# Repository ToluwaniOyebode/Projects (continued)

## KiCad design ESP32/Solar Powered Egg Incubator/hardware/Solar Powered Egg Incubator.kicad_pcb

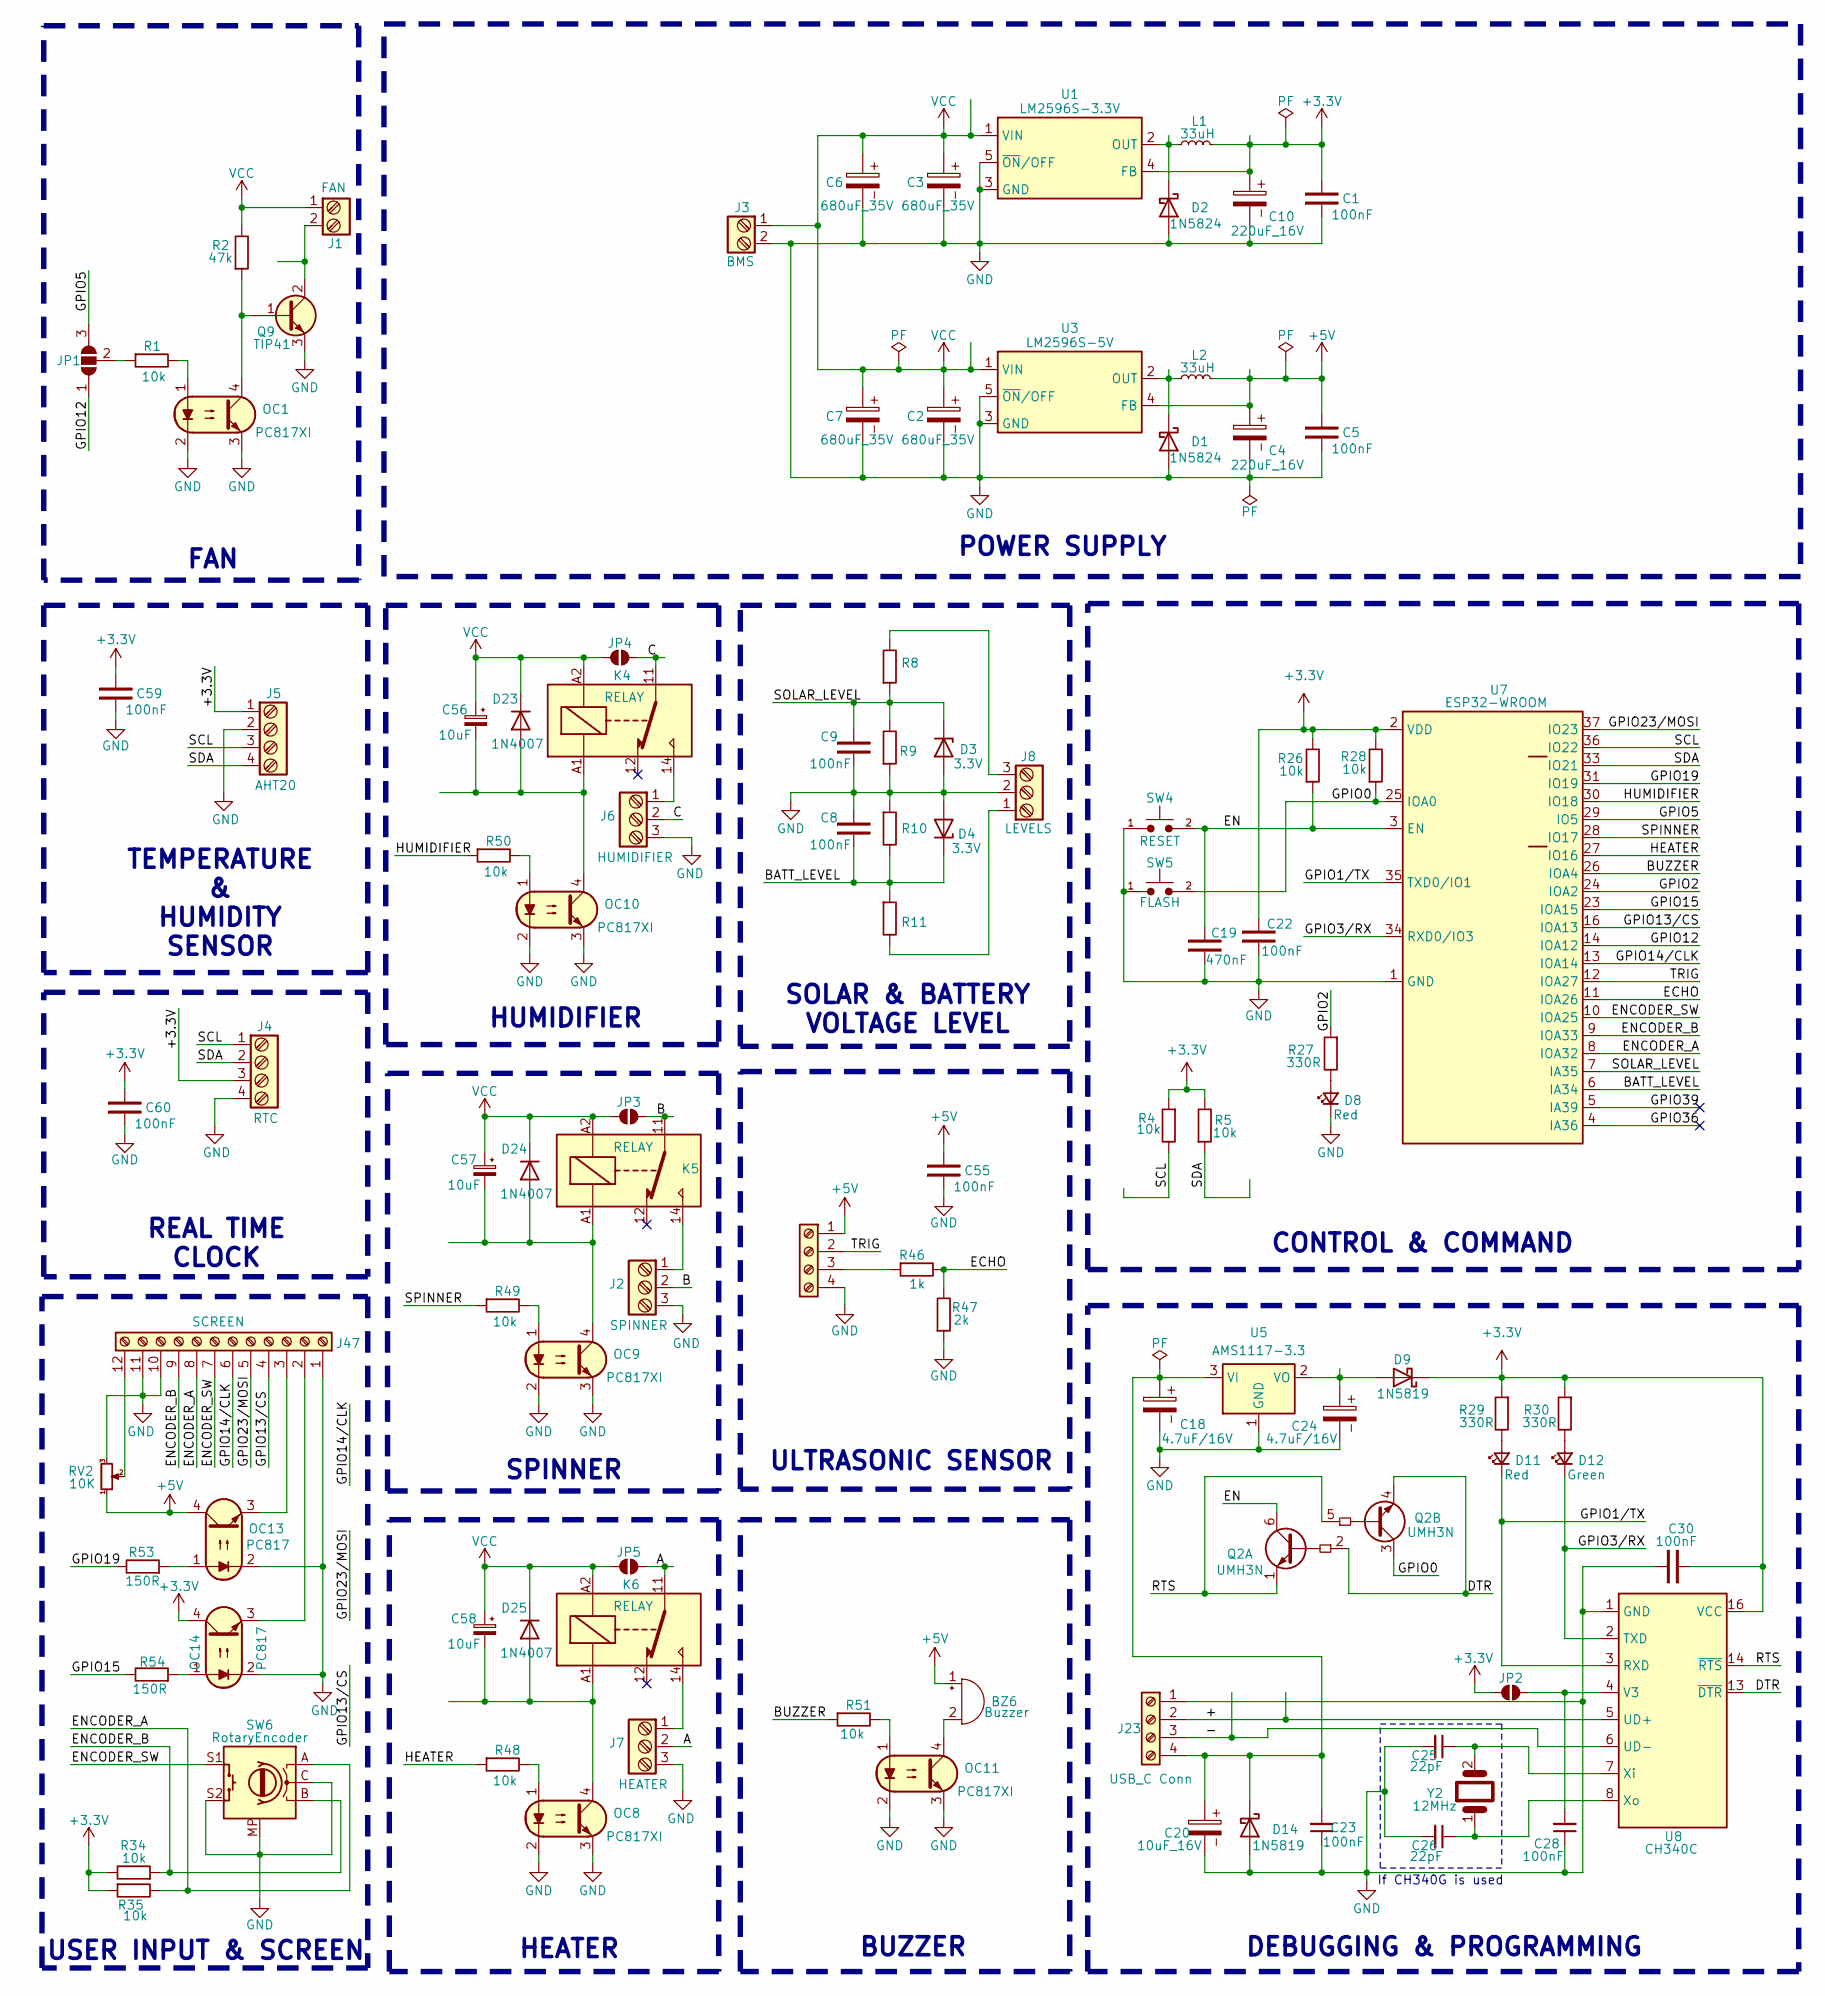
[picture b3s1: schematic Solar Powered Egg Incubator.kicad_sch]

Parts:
BZ6: Buzzer; Buzzer_15x7.5RM7.6
C1, C5, C8, C9, C22, C23, C28, C30, C55, C59, C60: 100nF; C_0805_2012Metric_Pad1.18x1.45mm_HandSolder
C2, C3, C6, C7: 680uF_35V; CP_Elec_10x12.5
C4, C10: 220uF_16V; CP_Elec_6.3x7.7
C18, C24: 4.7uF/16V; CP_EIA-3528-21_Kemet-B_HandSolder
C19: 470nF; C_0805_2012Metric_Pad1.18x1.45mm_HandSolder
C20: 10uF_16V; CP_Radial_D5.0mm_P2.00mm
C25, C26: 22pF; C_0805_2012Metric_Pad1.18x1.45mm_HandSolder
C56, C57, C58: 10uF; CP_EIA-3528-21_Kemet-B_HandSolder
D1, D2: 1N5824; D_SMA
D3, D4: 3.3V; D_SOD-123
D8, D11: Red; LED_D3.0mm
D9, D14: 1N5819; D_SMA
D12: Green; LED_D3.0mm
D23, D24, D25: 1N4007; D_SMA
J1: FAN; TerminalBlock_Phoenix_PT-1,5-2-5.0-H_1x02_P5.00mm_Horizontal
J2: SPINNER; TerminalBlock_Phoenix_MKDS-1,5-3_1x03_P5.00mm_Horizontal
J3: BMS; TerminalBlock_Phoenix_PT-1,5-2-5.0-H_1x02_P5.00mm_Horizontal
J4: RTC; PinHeader_1x04_P2.54mm_Vertical
J5: AHT20; PinHeader_1x04_P2.54mm_Vertical
J6: HUMIDIFIER; TerminalBlock_Phoenix_MKDS-1,5-3_1x03_P5.00mm_Horizontal
J7: HEATER; TerminalBlock_Phoenix_MKDS-1,5-3_1x03_P5.00mm_Horizontal
J8: LEVELS; PinHeader_1x03_P2.54mm_Vertical
J23: USB_C Conn; PinHeader_1x04_P2.54mm_Vertical
J42: Ultra Sonic; PinSocket_1x04_P2.54mm_Vertical
J47: SCREEN; PinHeader_1x12_P2.54mm_Vertical
JP1: SolderJumper_3_Open; SolderJumper-3_P1.3mm_Open_Pad1.0x1.5mm
JP2, JP3, JP4, JP5: SolderJumper-2_P1.3mm_Open_Pad1.0x1.5mm
K4, K5, K6: RELAY; Relay_SPDT_Finder_36.11
L1, L2: 33uH; L_12x12mm_H6mm
OC1, OC8, OC9, OC10, OC11: PC817XI; SMDIP-4_W9.53mm
OC13, OC14: PC817; SMDIP-4_W9.53mm
Q2: UMH3N; SOT-363_SC-70-6
Q9: TIP41; TO-220-3_Vertical
R1, R4, R5, R26, R28, R34, R35, R48, R49, R50, R51: 10k; R_0805_2012Metric
R2: 47k; R_0805_2012Metric
R8, R9, R10, R11: NS; R_0805_2012Metric
R27, R29, R30: 330R; R_0805_2012Metric
R46: 1k; R_0805_2012Metric
R47: 2k; R_0805_2012Metric
R53, R54: 150R; R_0805_2012Metric
RV2: 10K; Potentiometer_Bourns_3296W_Vertical
SW4: RESET; SW_SPST_CK_KXT3
SW5: FLASH; SW_SPST_CK_KXT3
SW6: RotaryEncoder; PinHeader_1x06_P2.54mm_Vertical
U1: LM2596S-3.3V; TO-263-5_TabPin6
U3: LM2596S-5V; TO-263-5_TabPin6
U5: AMS1117-3.3; SOT-223-3_TabPin2
U7: ESP32-WROOM; ESP32-WROOM-32
U8: CH340C; SOIC-16_3.9x9.9mm_P1.27mm
Y2: 12MHz; Crystal_HC49-4H_Vertical

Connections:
+3.3V: C1.2, C10.1, C22.2, C30.1, C59.2, C60.2, D9.1 (K), J4.3, J5.1, JP2.2 (B), L1.2, OC14.4, R4.1, R5.2, R26.2, R28.2, R29.1, R30.1, R34.2, R35.1, U1.4 (FB), U7.2 (VDD), U8.16 (VCC)
+5V: BZ6.1 (+), C4.1, C5.2, C55.2, J42.1, L2.2, OC13.4, RV2.1, U3.4 (FB)
/+: J23.2, U8.5 (UD+)
/-: J23.3, U8.6 (UD-)
/A: J7.2, JP5.1 (A), K6.11
/B: J2.2, JP3.1 (A), K5.11
/BATT_LEVEL: C8.1, D4.1 (K), R10.2, R11.1, U7.6 (IA34)
/BUZZER: R51.1, U7.26 (IOA4)
/C: J6.2, JP4.1 (A), K4.11
/DTR: Q2.2 (B1), Q2.4 (E2), U8.13 (~DTR)
/ECHO: R46.2, R47.2, U7.11 (IOA26)
/EN: C19.2, Q2.6 (C1), R26.1, SW4.2, U7.3 (EN)
/ENCODER_A: J47.8, R35.2, SW6.A, U7.8 (IOA32)
/ENCODER_B: J47.9, R34.1, SW6.B, U7.9 (IOA33)
/ENCODER_SW: J47.7, SW6.S1, U7.10 (IOA25)
/GPIO0: Q2.3 (C2), R28.1, SW5.2, U7.25 (IOA0)
/GPIO1/TX: D11.1 (K), U7.35 (TXD0/IO1), U8.3 (RXD)
/GPIO2: R27.1, U7.24 (IOA2)
/GPIO3/RX: D12.1 (K), U7.34 (RXD0/IO3), U8.2 (TXD)
/GPIO5: JP1.3 (B), U7.29 (IO5)
/GPIO12: JP1.1 (A), U7.14 (IOA12)
/GPIO13/CS: J47.4, U7.16 (IOA13)
/GPIO14/CLK: J47.6, U7.13 (IOA14)
/GPIO15: R54.2, U7.23 (IOA15)
/GPIO19: R53.2, U7.31 (IO19)
/GPIO23/MOSI: J47.5, U7.37 (IO23)
/GPIO36: U7.4 (IA36)
/GPIO39: U7.5 (IA39)
/HEATER: R48.1, U7.27 (IO16)
/HUMIDIFIER: R50.1, U7.30 (IO18)
/RTS: Q2.1 (E1), Q2.5 (B2), U8.14 (~RTS)
/SCL: J4.1, J5.3, R4.2, U7.36 (IO22)
/SDA: J4.2, J5.4, R5.1, U7.33 (IO21)
/SOLAR_LEVEL: C9.2, D3.1 (K), R8.1, R9.2, U7.7 (IA35)
/SPINNER: R49.1, U7.28 (IO17)
/TRIG: J42.2, U7.12 (IOA27)
GND: C1.1, C2.2, C3.2, C4.2, C5.1, C6.2, C7.2, C8.2, C9.1, C10.2, C18.2, C19.1, C20.2, C22.1, C23.1, C24.2, C25.2, C26.2, C28.1, C30.2, C55.1, C59.1, C60.1, D1.2 (A), D2.2 (A), D3.2 (A), D4.2 (A), D8.1 (K), D14.2 (A), J2.3, J3.2, J4.4, J5.2, J6.3, J7.3, J8.2, J23.1, J42.4, J47.1, J47.10, J47.11, OC1.2, OC1.3, OC8.2, OC8.3, OC9.2, OC9.3, OC10.2, OC10.3, OC11.2, OC11.3, OC13.2, OC14.2, Q9.3 (E), R9.1, R10.1, R47.1, RV2.3, SW4.1, SW5.1, SW6.C, SW6.MP, SW6.S2, U1.3 (GND), U1.5 (~ON/OFF), U1.6 (GND), U3.3 (GND), U3.5 (~ON/OFF), U3.6 (GND), U5.1 (GND), U7.1 (GND), U7.15 (GND), U7.38 (GND), U7.39 (GND), U8.1 (GND)
unnamed: BZ6.2 (-), OC11.4
unnamed: D1.1 (K), L2.1, U3.2 (OUT)
unnamed: D2.1 (K), L1.1, U1.2 (OUT)
unnamed: D8.2 (A), R27.2
unnamed: C24.1, D9.2 (A), U5.2 (VO)
unnamed: D11.2 (A), R29.2
unnamed: D12.2 (A), R30.2
unnamed: C18.1, C20.1, C23.2, D14.1 (K), J23.4, U5.3 (VI)
unnamed: C56.2, D23.2 (A), K4.A1, OC10.4
unnamed: C57.2, D24.2 (A), K5.A1, OC9.4
unnamed: C58.2, D25.2 (A), K6.A1, OC8.4
unnamed: J2.1, K5.14
unnamed: J6.1, K4.14
unnamed: J7.1, K6.14
unnamed: J8.1, R11.2
unnamed: J8.3, R8.2
unnamed: J42.3, R46.1
unnamed: J47.2, OC14.3
unnamed: J47.3, OC13.3
unnamed: J47.12, RV2.2
unnamed: JP1.2 (C), R1.1
unnamed: C28.2, JP2.1 (A), U8.4 (V3)
unnamed: OC1.1, R1.2
unnamed: OC8.1, R48.2
unnamed: OC9.1, R49.2
unnamed: OC10.1, R50.2
unnamed: OC11.1, R51.2
unnamed: OC13.1, R53.1
unnamed: OC14.1, R54.1
unnamed: OC1.4, Q9.1 (B), R2.1
unnamed: J1.2, Q9.2 (C)
unnamed: C25.1, U8.7 (Xi), Y2.2
unnamed: C26.1, U8.8 (Xo), Y2.1
VCC: C2.1, C3.1, C6.1, C7.1, C56.1, C57.1, C58.1, D23.1 (K), D24.1 (K), D25.1 (K), J1.1, J3.1, JP3.2 (B), JP4.2 (B), JP5.2 (B), K4.A2, K5.A2, K6.A2, R2.2, U1.1 (VIN), U3.1 (VIN)

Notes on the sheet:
HUMIDIFIER
DEBUGGING & PROGRAMMING
CONTROL & COMMAND
ULTRASONIC SENSOR
REAL TIME CLOCK
SPINNER
HEATER
If CH340G is used
POWER SUPPLY
BUZZER
TEMPERATURE & HUMIDITY SENSOR
USER INPUT & SCREEN
FAN
SOLAR & BATTERY VOLTAGE LEVEL

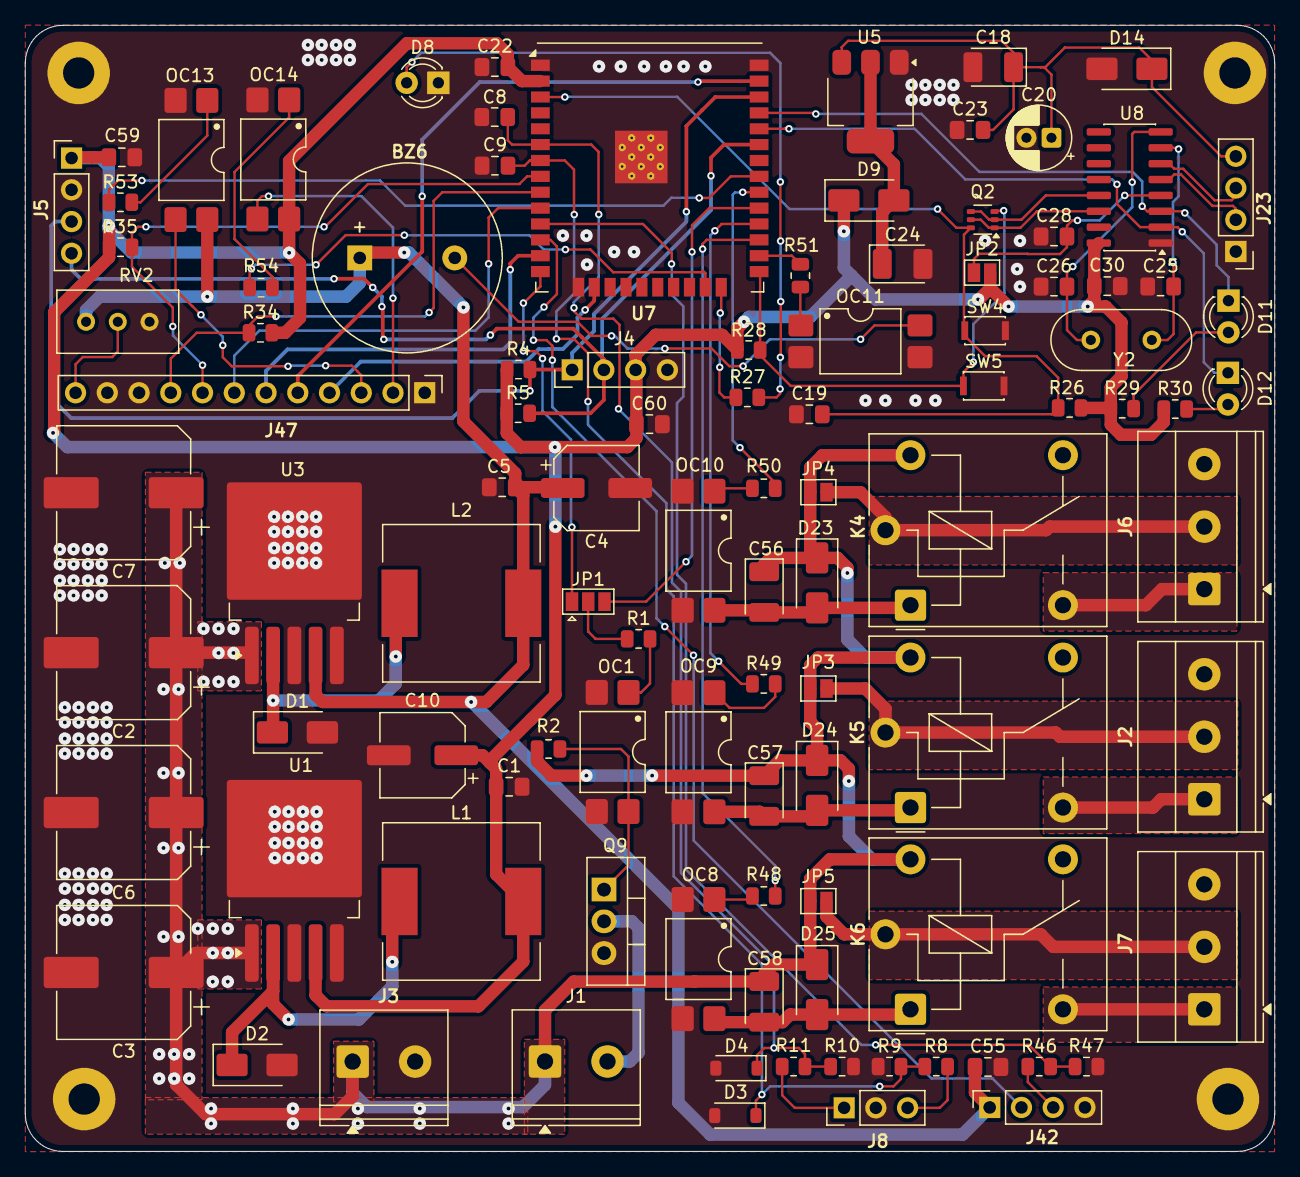
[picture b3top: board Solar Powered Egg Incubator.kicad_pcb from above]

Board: 2 copper layers, 100.0 x 90.1 mm, 101 parts (0 on the bottom side), 69 nets.

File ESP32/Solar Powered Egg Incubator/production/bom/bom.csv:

Designator,Footprint,Quantity,Value,LCSC Part #
BZ6,Buzzer_15x7.5RM7.6,1,Buzzer,
"C1, C22, C23, C28, C30, C5, C55, C59, C60, C8, C9",0805,11,100nF,
"C10, C4",CP_Elec_6.3x7.7,2,220uF_16V,
"C18, C24",CP_EIA-3528-21_Kemet-B_HandSolder,2,4.7uF/16V,
C19,0805,1,470nF,
"C2, C3, C6, C7",CP_Elec_10x12.5,4,680uF_35V,
C20,CP_Radial_D5.0mm_P2.00mm,1,10uF_16V,
"C25, C26",0805,2,22pF,
"C56, C57, C58",CP_EIA-3528-21_Kemet-B_HandSolder,3,10uF,
"D1, D2",D_SMA,2,1N5824,
"D11, D8",LED_D3.0mm,2,Red,
D12,LED_D3.0mm,1,Green,
"D14, D9",D_SMA,2,1N5819,
"D23, D24, D25",D_SMA,3,1N4007,
"D3, D4",D_SOD-123,2,3.3V,
J1,"TerminalBlock_Phoenix_PT-1,5-2-5.0-H_1x02_P5.00mm_Horizontal",1,FAN,
J2,"TerminalBlock_Phoenix_MKDS-1,5-3_1x03_P5.00mm_Horizontal",1,SPINNER,
J23,PinHeader_1x04_P2.54mm_Vertical,1,USB_C Conn,
J3,"TerminalBlock_Phoenix_PT-1,5-2-5.0-H_1x02_P5.00mm_Horizontal",1,BMS,
J4,PinHeader_1x04_P2.54mm_Vertical,1,RTC,
J42,PinSocket_1x04_P2.54mm_Vertical,1,Ultra Sonic,
J47,PinHeader_1x12_P2.54mm_Vertical,1,SCREEN,
J5,PinHeader_1x04_P2.54mm_Vertical,1,AHT20,
J6,"TerminalBlock_Phoenix_MKDS-1,5-3_1x03_P5.00mm_Horizontal",1,HUMIDIFIER,
J7,"TerminalBlock_Phoenix_MKDS-1,5-3_1x03_P5.00mm_Horizontal",1,HEATER,
J8,PinHeader_1x03_P2.54mm_Vertical,1,LEVELS,
"JP2, JP3, JP4, JP5",SolderJumper-2_P1.3mm_Open_Pad1.0x1.5mm,4,~,
"K4, K5, K6",Relay_SPDT_Finder_36.11,3,RELAY,
"L1, L2",L_12x12mm_H6mm,2,33uH,
"OC1, OC10, OC11, OC8, OC9",SMDIP-4_W9.53mm,5,PC817XI,
"OC13, OC14",SMDIP-4_W9.53mm,2,PC817,
Q2,SOT-363_SC-70-6,1,UMH3N,
Q9,TO-220-3_Vertical,1,TIP41,
"R1, R26, R28, R34, R35, R4, R48, R49, R5, R50, R51",0805,11,10k,
"R10, R11, R8, R9",0805,4,NS,
R2,0805,1,47k,
"R27, R29, R30",0805,3,330R,
R46,0805,1,1k,
R47,0805,1,2k,
"R53, R54",0805,2,150R,
RV2,Potentiometer_Bourns_3296W_Vertical,1,10K,
SW4,SW_SPST_CK_KXT3,1,RESET,
SW5,SW_SPST_CK_KXT3,1,FLASH,
U1,TO-263-5_TabPin6,1,LM2596S-3.3V,
U3,TO-263-5_TabPin6,1,LM2596S-5V,
U5,SOT-223-3_TabPin2,1,AMS1117-3.3,
U7,ESP32-WROOM-32,1,ESP32-WROOM,
U8,SOIC-16_3.9x9.9mm_P1.27mm,1,CH340C,
Y2,Crystal_HC49-4H_Vertical,1,12MHz,

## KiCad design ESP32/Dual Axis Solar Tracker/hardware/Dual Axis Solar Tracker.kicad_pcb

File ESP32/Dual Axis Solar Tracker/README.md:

# Dual Axis Solar Tracker
Generated using KiCad Industrial Setup Script

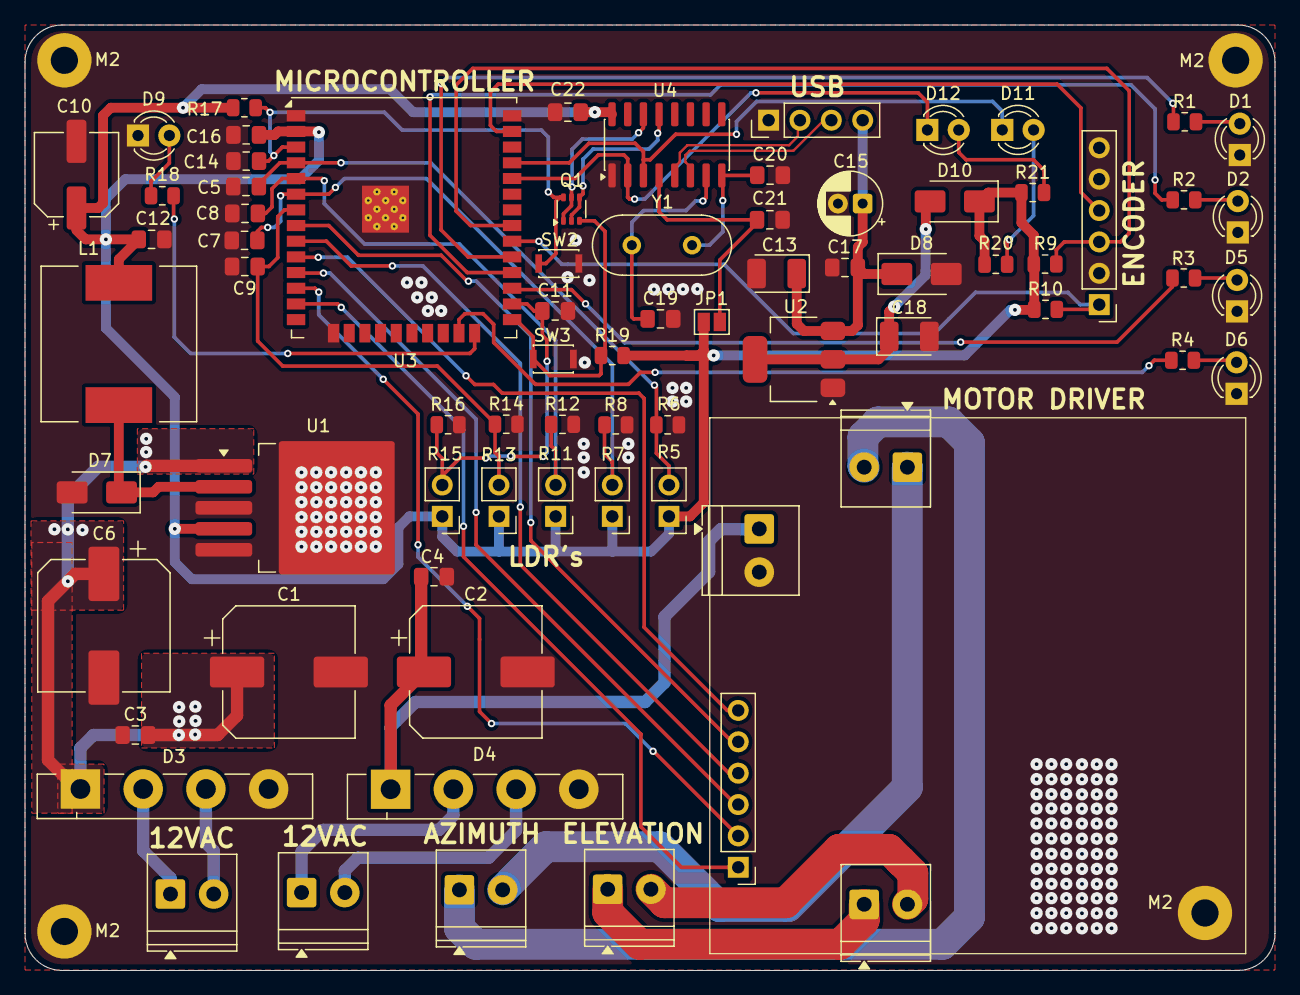
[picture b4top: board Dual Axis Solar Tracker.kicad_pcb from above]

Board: 2 copper layers, 101.2 x 76.6 mm, 80 parts (1 on the bottom side), 52 nets.

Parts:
 : LOGO; CULogo
C1, C2: 470uF/25V; CP_Elec_10x12.5
C3, C4, C5, C7, C8, C9, C11, C12, C16, C17, C21, C22: 100nF; C_0805_2012Metric_Pad1.18x1.45mm_HandSolder
C6: 680uF_35V; CP_Elec_10x12.5
C10: 220uF_16V; CP_Elec_6.3x7.7
C13, C18: 4.7uF/16V; CP_EIA-3528-21_Kemet-B_HandSolder
C14: 470nF; C_0805_2012Metric_Pad1.18x1.45mm_HandSolder
C15: 10uF_16V; CP_Radial_D5.0mm_P2.00mm
C19, C20: 22pF; C_0805_2012Metric_Pad1.18x1.45mm_HandSolder
D1, D2, D5, D6, D9, D11: Red; LED_D3.0mm
D3, D4: GBU8M; Diode_Bridge_Vishay_GBU
D7: 1N5824; D_SMA
D8, D10: 1N5819; D_SMA
D12: Green; LED_D3.0mm
J1, J2: 12VAC; TerminalBlock_Phoenix_PT-1,5-2-3.5-H_1x02_P3.50mm_Horizontal
J3, J5: MOTOR; TerminalBlock_Phoenix_PT-1,5-2-3.5-H_1x02_P3.50mm_Horizontal
J4: SIGNAL; PinHeader_1x06_P2.54mm_Vertical
J6: 12V_IN; TerminalBlock_Phoenix_PT-1,5-2-3.5-H_1x02_P3.50mm_Horizontal
J7: USB_C Conn; PinHeader_1x04_P2.54mm_Vertical
JP1: SolderJumper-2_P1.3mm_Open_Pad1.0x1.5mm
L1: 33uH; L_12x12mm_H6mm
M1, M2: Geared Motor; TerminalBlock_Phoenix_PT-1,5-2-3.5-H_1x02_P3.50mm_Horizontal
M2#2, M2#3, M2#4, M2#5: MountingHole_2.2mm_M2_Pad
Q1: UMH3N; SOT-363_SC-70-6
R1, R2, R3, R4, R18, R20, R21: 330R; R_0805_2012Metric
R5, R7, R11, R13, R15: LDR; PinHeader_1x02_P2.54mm_Vertical
R6, R8, R9, R10, R12, R14, R16, R17, R19: 10k; R_0805_2012Metric
SW1: RotaryEncoder; PinHeader_1x06_P2.54mm_Vertical
SW2: RESET; SW_SPST_CK_KXT3
SW3: FLASH; SW_SPST_CK_KXT3
U1: LM2596S-3.3V; TO-263-5_TabPin6
U2: AMS1117-3.3; SOT-223-3_TabPin2
U3: ESP32-WROOM; ESP32-WROOM-32U
U4: CH340C; SOIC-16_3.9x9.9mm_P1.27mm
Y1: 12MHz; Crystal_HC49-4H_Vertical

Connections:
+3.3V: C10.1, C12.2, C16.2, C22.1, D10.1 (K), JP1.2 (B), L1.2, R5.1, R7.1, R9.2, R10.1, R11.1, R13.1, R15.1, R17.2, R19.2, R20.1, R21.1, U1.4 (FB), U3.2 (VDD), U4.16 (VCC)
+12V: C2.1, C4.2, D4.1 (+), J6.1
/+: J7.2, U4.5 (UD+)
/-: J7.3, U4.6 (UD-)
/DTR: Q1.2 (B1), Q1.4 (E2), U4.13 (~DTR)
/EN: C14.2, Q1.6 (C1), R17.1, SW2.2, U3.3 (EN)
/GPIO0: Q1.3 (C2), R19.1, SW3.2, U3.25 (IOA0)
/GPIO1/TX: D11.1 (K), U3.35 (TXD0/IO1), U4.3 (RXD)
/GPIO2: R18.1, U3.24 (IOA2)
/GPIO3/RX: D12.1 (K), U3.34 (RXD0/IO3), U4.2 (TXD)
/GPIO4: C11.1, R15.2, R16.1, U3.26 (IOA4)
/GPIO5: R1.1, U3.29 (IO5)
/GPIO14: J4.1, U3.13 (IOA14)
/GPIO15: R4.1, U3.23 (IOA15)
/GPIO16: R3.1, U3.27 (IO16)
/GPIO17: R2.1, U3.28 (IO17)
/GPIO18: R10.2, SW1.1 (A), U3.30 (IO18)
/GPIO19: R9.1, SW1.3 (B), U3.31 (IO19)
/GPIO23: SW1.4 (S1), U3.37 (IO23)
/GPIO25: J4.6, U3.10 (IOA25)
/GPIO26: J4.3, U3.11 (IOA26)
/GPIO27: J4.2, U3.12 (IOA27)
/GPIO32: J4.5, U3.8 (IOA32)
/GPIO33: J4.4, U3.9 (IOA33)
/GPIO34: C7.1, R7.2, R8.1, U3.6 (IA34)
/GPIO35: C9.1, R13.2, R14.1, U3.7 (IA35)
/GPIO36: C5.1, R5.2, R6.1, U3.4 (IA36)
/GPIO39: C8.1, R11.2, R12.1, U3.5 (IA39)
/RTS: Q1.1 (E1), Q1.5 (B2), U4.14 (~RTS)
GND: C1.2, C2.2, C3.1, C4.1, C5.2, C6.2, C7.2, C8.2, C9.2, C10.2, C11.2, C12.1, C13.2, C14.1, C15.2, C16.1, C17.1, C18.2, C19.2, C20.2, C21.1, C22.2, D1.1 (K), D2.1 (K), D3.4 (-), D4.4 (-), D5.1 (K), D6.1 (K), D7.2 (A), D8.2 (A), D9.1 (K), J6.2, J7.1, M2#2.1, M2#3.1, M2#4.1, M2#5.1, R6.2, R8.2, R12.2, R14.2, R16.2, SW1.2 (C), SW1.5 (S2), SW1.6 (MP), SW2.1, SW3.1, U1.3 (GND), U1.5 (~ON/OFF), U1.6 (GND), U2.1 (GND), U3.1 (GND), U3.15 (GND), U3.38 (GND), U3.39 (GND), U4.1 (GND)
unnamed: D1.2 (A), R1.2
unnamed: D2.2 (A), R2.2
unnamed: D5.2 (A), R3.2
unnamed: D6.2 (A), R4.2
unnamed: D7.1 (K), L1.1, U1.2 (OUT)
unnamed: C13.1, C15.1, C17.2, D8.1 (K), J7.4, U2.3 (VI)
unnamed: D9.2 (A), R18.2
unnamed: C18.1, D10.2 (A), U2.2 (VO)
unnamed: D11.2 (A), R20.2
unnamed: D12.2 (A), R21.2
unnamed: D3.2, J1.1
unnamed: D3.3, J1.2
unnamed: D4.2, J2.1
unnamed: D4.3, J2.2
unnamed: J3.1, M1.2 (-)
unnamed: J3.2, M1.1 (+)
unnamed: J5.1, M2.1 (+)
unnamed: J5.2, M2.2 (-)
unnamed: C21.2, JP1.1 (A), U4.4 (V3)
unnamed: C19.1, U4.7 (Xi), Y1.2
unnamed: C20.1, U4.8 (Xo), Y1.1
VCC: C1.1, C3.2, C6.1, D3.1 (+), U1.1 (VIN)

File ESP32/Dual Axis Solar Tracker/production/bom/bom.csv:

Designator,Footprint,Quantity,Value,LCSC Part #
"C1, C2",CP_Elec_10x12.5,2,470uF/25V,
C10,CP_Elec_6.3x7.7,1,220uF_16V,
"C11, C12, C16, C17, C21, C22, C3, C4, C5, C7, C8, C9",0805,12,100nF,
"C13, C18",CP_EIA-3528-21_Kemet-B_HandSolder,2,4.7uF/16V,
C14,0805,1,470nF,
C15,CP_Radial_D5.0mm_P2.00mm,1,10uF_16V,
"C19, C20",0805,2,22pF,
C6,CP_Elec_10x12.5,1,680uF_35V,
"D1, D11, D2, D5, D6, D9",LED_D3.0mm,6,Red,
"D10, D8",D_SMA,2,1N5819,
D12,LED_D3.0mm,1,Green,
"D3, D4",Diode_Bridge_Vishay_GBU,2,GBU8M,
D7,D_SMA,1,1N5824,
"J1, J2","TerminalBlock_Phoenix_PT-1,5-2-3.5-H_1x02_P3.50mm_Horizontal",2,12VAC,
"J3, J5","TerminalBlock_Phoenix_PT-1,5-2-3.5-H_1x02_P3.50mm_Horizontal",2,MOTOR,
J4,PinHeader_1x06_P2.54mm_Vertical,1,SIGNAL,
J6,"TerminalBlock_Phoenix_PT-1,5-2-3.5-H_1x02_P3.50mm_Horizontal",1,12V_IN,
J7,PinHeader_1x04_P2.54mm_Vertical,1,USB_C Conn,
JP1,SolderJumper-2_P1.3mm_Open_Pad1.0x1.5mm,1,~,
L1,L_12x12mm_H6mm,1,33uH,
"M1, M2_5","TerminalBlock_Phoenix_PT-1,5-2-3.5-H_1x02_P3.50mm_Horizontal",2,Geared Motor,
Q1,SOT-363_SC-70-6,1,UMH3N,
"R1, R18, R2, R20, R21, R3, R4",0805,7,330R,
"R10, R12, R14, R16, R17, R19, R6, R8, R9",0805,9,10k,
"R11, R13, R15, R5, R7",PinHeader_1x02_P2.54mm_Vertical,5,LDR,
SW1,PinHeader_1x06_P2.54mm_Vertical,1,RotaryEncoder,
SW2,SW_SPST_CK_KXT3,1,RESET,
SW3,SW_SPST_CK_KXT3,1,FLASH,
U1,TO-263-5_TabPin6,1,LM2596S-3.3V,
U2,SOT-223-3_TabPin2,1,AMS1117-3.3,
U3,ESP32-WROOM-32U,1,ESP32-WROOM,
U4,SOIC-16_3.9x9.9mm_P1.27mm,1,CH340C,
Y1,Crystal_HC49-4H_Vertical,1,12MHz,

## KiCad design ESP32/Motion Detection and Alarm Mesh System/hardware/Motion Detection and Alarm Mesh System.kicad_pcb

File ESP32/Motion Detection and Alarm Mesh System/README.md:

# Motion Detection and Alarm Mesh System
Generated using KiCad Industrial Setup Script

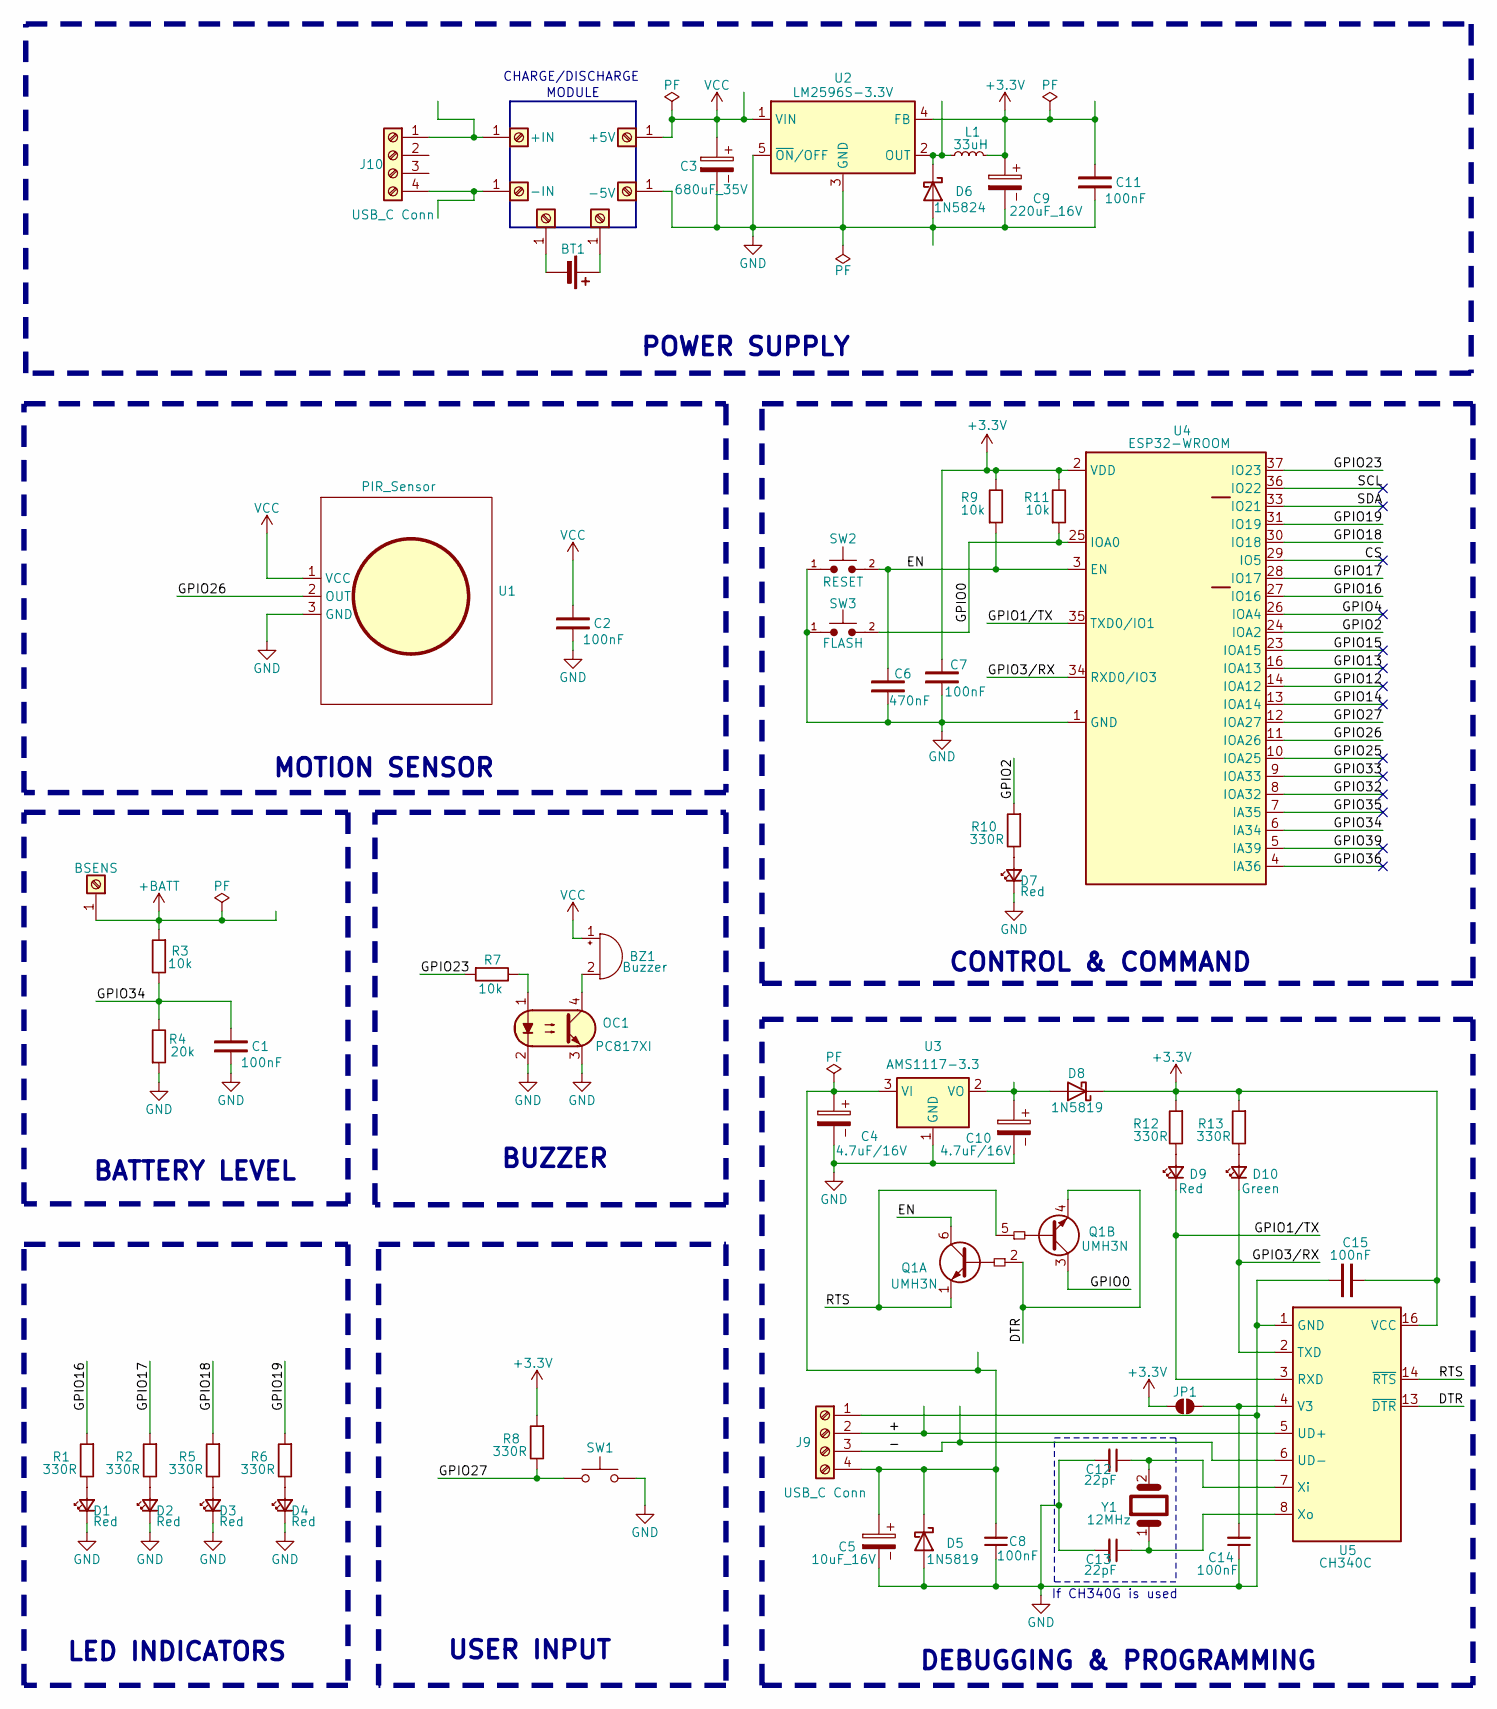
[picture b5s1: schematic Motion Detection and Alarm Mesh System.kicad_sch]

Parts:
BT1: Battery_Cell
BZ1: Buzzer; Buzzer_15x7.5RM7.6
C1, C2, C7, C8, C11, C14, C15: 100nF; C_0805_2012Metric_Pad1.18x1.45mm_HandSolder
C3: 680uF_35V; CP_Elec_10x12.5
C4, C10: 4.7uF/16V; CP_EIA-3528-21_Kemet-B_HandSolder
C5: 10uF_16V; CP_Radial_D5.0mm_P2.00mm
C6: 470nF; C_0805_2012Metric_Pad1.18x1.45mm_HandSolder
C9: 220uF_16V; CP_Elec_6.3x7.7
C12, C13: 22pF; C_0805_2012Metric_Pad1.18x1.45mm_HandSolder
D1, D2, D3, D4, D7, D9: Red; LED_D3.0mm
D5, D8: 1N5819; D_SMA
D6: 1N5824; D_SMA
D10: Green; LED_D3.0mm
J1: BSENS; SolderWire-0.1sqmm_1x01_D0.4mm_OD1mm
J3: +IN; TestPoint_Keystone_5015_Micro_Mini
J4: -IN; TestPoint_Keystone_5015_Micro_Mini
J5: -BATT
J6: +BATT
J7: +5V; TestPoint_Keystone_5015_Micro_Mini
J8: -5V; TestPoint_Keystone_5015_Micro_Mini
J9, J10: USB_C Conn; PinHeader_1x04_P2.54mm_Vertical
JP1: SolderJumper-2_P1.3mm_Open_Pad1.0x1.5mm
L1: 33uH; L_12x12mm_H6mm
OC1: PC817XI; SMDIP-4_W9.53mm
Q1: UMH3N; SOT-363_SC-70-6
R1, R2, R5, R6, R8, R10, R12, R13: 330R; R_0805_2012Metric
R3, R7, R9, R11: 10k; R_0805_2012Metric
R4: 20k; R_0805_2012Metric
SW1: SW_Push; PinHeader_1x02_P2.54mm_Vertical
SW2: RESET; SW_SPST_CK_KXT3
SW3: FLASH; SW_SPST_CK_KXT3
U1: PIR_Sensor; PinHeader_1x03_P2.54mm_Vertical
U2: LM2596S-3.3V; TO-263-5_TabPin6
U3: AMS1117-3.3; SOT-223-3_TabPin2
U4: ESP32-WROOM; ESP32-WROOM-32U
U5: CH340C; SOIC-16_3.9x9.9mm_P1.27mm
Y1: 12MHz; Crystal_HC49-4H_Vertical

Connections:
+3.3V: C7.2, C9.1, C11.2, C15.1, D8.1 (K), JP1.2 (B), L1.2, R8.1, R9.2, R11.2, R12.1, R13.1, U2.4 (FB), U4.2 (VDD), U5.16 (VCC)
+BATT: J1.1, R3.1
/+: J9.2, U5.5 (UD+)
/-: J9.3, U5.6 (UD-)
/CS: U4.29 (IO5)
/DTR: Q1.2 (B1), Q1.4 (E2), U5.13 (~DTR)
/EN: C6.2, Q1.6 (C1), R9.1, SW2.2, U4.3 (EN)
/GPIO0: Q1.3 (C2), R11.1, SW3.2, U4.25 (IOA0)
/GPIO1/TX: D9.1 (K), U4.35 (TXD0/IO1), U5.3 (RXD)
/GPIO2: R10.1, U4.24 (IOA2)
/GPIO3/RX: D10.1 (K), U4.34 (RXD0/IO3), U5.2 (TXD)
/GPIO4: U4.26 (IOA4)
/GPIO12: U4.14 (IOA12)
/GPIO13: U4.16 (IOA13)
/GPIO14: U4.13 (IOA14)
/GPIO15: U4.23 (IOA15)
/GPIO16: R1.1, U4.27 (IO16)
/GPIO17: R2.1, U4.28 (IO17)
/GPIO18: R5.1, U4.30 (IO18)
/GPIO19: R6.1, U4.31 (IO19)
/GPIO23: R7.1, U4.37 (IO23)
/GPIO25: U4.10 (IOA25)
/GPIO26: U1.2 (OUT), U4.11 (IOA26)
/GPIO27: R8.2, SW1.1, U4.12 (IOA27)
/GPIO32: U4.8 (IOA32)
/GPIO33: U4.9 (IOA33)
/GPIO34: C1.2, R3.2, R4.2, U4.6 (IA34)
/GPIO35: U4.7 (IA35)
/GPIO36: U4.4 (IA36)
/GPIO39: U4.5 (IA39)
/RTS: Q1.1 (E1), Q1.5 (B2), U5.14 (~RTS)
/SCL: U4.36 (IO22)
/SDA: U4.33 (IO21)
GND: C1.1, C2.1, C3.2, C4.2, C5.2, C6.1, C7.1, C8.1, C9.2, C10.2, C11.1, C12.2, C13.2, C14.1, C15.2, D1.1 (K), D2.1 (K), D3.1 (K), D4.1 (K), D5.2 (A), D6.2 (A), D7.1 (K), J8.1, J9.1, OC1.2, OC1.3, R4.1, SW1.2, SW2.1, SW3.1, U1.3 (GND), U2.3 (GND), U2.5 (~ON/OFF), U2.6 (GND), U3.1 (GND), U4.1 (GND), U4.15 (GND), U4.38 (GND), U4.39 (GND), U5.1 (GND)
unnamed: BT1.1 (+), J6.1
unnamed: BT1.2 (-), J5.1
unnamed: BZ1.2 (-), OC1.4
unnamed: D1.2 (A), R1.2
unnamed: D2.2 (A), R2.2
unnamed: D3.2 (A), R5.2
unnamed: D4.2 (A), R6.2
unnamed: C4.1, C5.1, C8.2, D5.1 (K), J9.4, U3.3 (VI)
unnamed: D6.1 (K), L1.1, U2.2 (OUT)
unnamed: D7.2 (A), R10.2
unnamed: C10.1, D8.2 (A), U3.2 (VO)
unnamed: D9.2 (A), R12.2
unnamed: D10.2 (A), R13.2
unnamed: J3.1, J10.1
unnamed: J4.1, J10.4
unnamed: C14.2, JP1.1 (A), U5.4 (V3)
unnamed: OC1.1, R7.2
unnamed: C12.1, U5.7 (Xi), Y1.2
unnamed: C13.1, U5.8 (Xo), Y1.1
VCC: BZ1.1 (+), C2.2, C3.1, J7.1, U1.1 (VCC), U2.1 (VIN)

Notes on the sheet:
MOTION SENSOR
MODULE
BUZZER
POWER SUPPLY
CHARGE/DISCHARGE
If CH340G is used
BATTERY LEVEL
LED INDICATORS
DEBUGGING & PROGRAMMING
CONTROL & COMMAND
USER INPUT

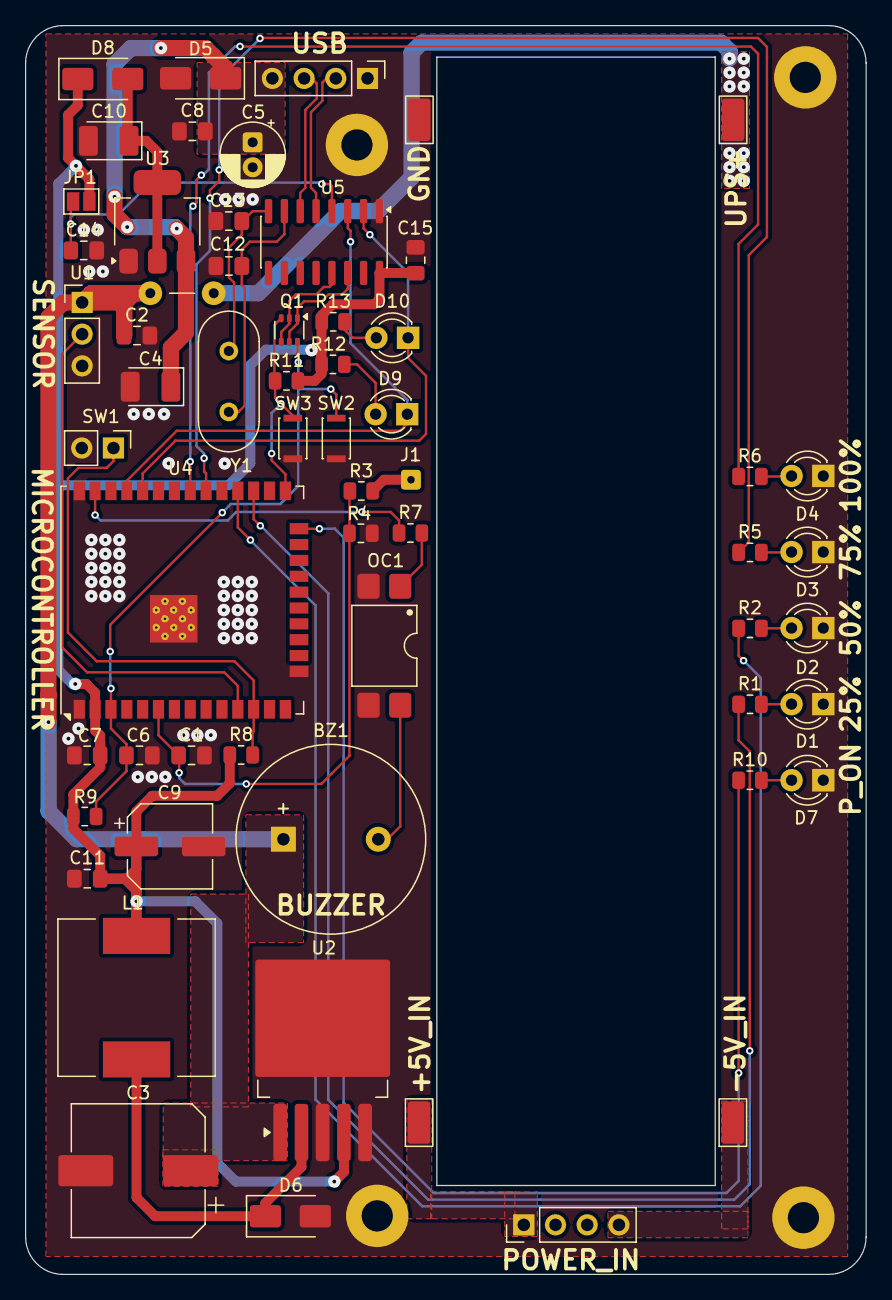
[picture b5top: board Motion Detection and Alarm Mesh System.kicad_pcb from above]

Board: 2 copper layers, 67.3 x 100.0 mm, 59 parts (0 on the bottom side), 38 nets.

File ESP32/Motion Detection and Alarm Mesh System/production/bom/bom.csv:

Designator,Footprint,Quantity,Value,LCSC Part #
BZ1,Buzzer_15x7.5RM7.6,1,Buzzer,
"C1, C11, C14, C15, C2, C7, C8",0805,7,100nF,
"C10, C4",CP_EIA-3528-21_Kemet-B_HandSolder,2,4.7uF/16V,
"C12, C13",0805,2,22pF,
C3,CP_Elec_10x12.5,1,680uF_35V,
C5,CP_Radial_D5.0mm_P2.00mm,1,10uF_16V,
C6,0805,1,470nF,
C9,CP_Elec_6.3x7.7,1,220uF_16V,
"D1, D2, D3, D4, D7, D9",LED_D3.0mm,6,Red,
D10,LED_D3.0mm,1,Green,
"D5, D8",D_SMA,2,1N5819,
D6,D_SMA,1,1N5824,
J1,SolderWire-0.1sqmm_1x01_D0.4mm_OD1mm,1,BSENS,
"J10, J9",PinHeader_1x04_P2.54mm_Vertical,2,USB_C Conn,
J3,TestPoint_Keystone_5015_Micro_Mini,1,+IN,
J4,TestPoint_Keystone_5015_Micro_Mini,1,-IN,
J7,TestPoint_Keystone_5015_Micro_Mini,1,+5V,
J8,TestPoint_Keystone_5015_Micro_Mini,1,-5V,
JP1,SolderJumper-2_P1.3mm_Open_Pad1.0x1.5mm,1,~,
L1,L_12x12mm_H6mm,1,33uH,
OC1,SMDIP-4_W9.53mm,1,PC817XI,
Q1,SOT-363_SC-70-6,1,UMH3N,
"R1, R10, R12, R13, R2, R5, R6, R8",0805,8,330R,
"R11, R3, R7, R9",0805,4,10k,
R4,0805,1,20k,
SW1,PinHeader_1x02_P2.54mm_Vertical,1,SW_Push,
SW2,SW_SPST_CK_KXT3,1,RESET,
SW3,SW_SPST_CK_KXT3,1,FLASH,
U1,PinHeader_1x03_P2.54mm_Vertical,1,PIR_Sensor,
U2,TO-263-5_TabPin6,1,LM2596S-3.3V,
U3,SOT-223-3_TabPin2,1,AMS1117-3.3,
U4,ESP32-WROOM-32U,1,ESP32-WROOM,
U5,SOIC-16_3.9x9.9mm_P1.27mm,1,CH340C,
Y1,Crystal_HC49-4H_Vertical,1,12MHz,
